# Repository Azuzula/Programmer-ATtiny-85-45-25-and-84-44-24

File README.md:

# Programmer ATtiny 85/45/25 and 84/44/24
Scheme and PCB made in the Eagle 8.7.1
Added Gerber files.

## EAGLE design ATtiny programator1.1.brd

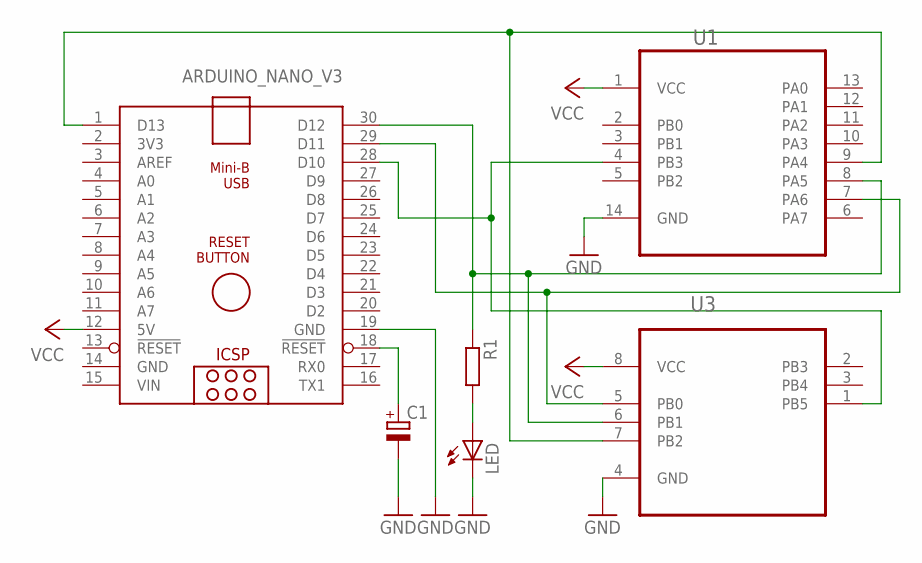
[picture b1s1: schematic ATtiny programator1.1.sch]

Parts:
ARDUINO_NANO_V3: ARDUINO_NANO
C1: CPOL-EUTT2D4; TT2D4
LED: LED3MM
R1: R0204/7; 0204/7
U1: ATTINY84-20PU; DIP254P762X533-14
U3: ATTINY45-20PU; DIP254P762X533-8

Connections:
GND: ARDUINO_NANO_V3.14 (GND), ARDUINO_NANO_V3.19 (GND), C1.-, LED.K (C), U1.14 (GND), U3.4 (GND)
MISO: ARDUINO_NANO_V3.30 (D12), R1.1, U1.8 (PA5), U3.6 (PB1)
MOSI: ARDUINO_NANO_V3.29 (D11), U1.7 (PA6), U3.5 (PB0)
unnamed: LED.A, R1.2
unnamed: ARDUINO_NANO_V3.18 (!RESET), C1.+
SCK: ARDUINO_NANO_V3.1 (D13), U1.9 (PA4), U3.7 (PB2)
SS: ARDUINO_NANO_V3.28 (D10), U1.4 (PB3), U3.1 (PB5)
VCC: ARDUINO_NANO_V3.12 (5V), U1.1 (VCC), U3.8 (VCC)
VIN: ARDUINO_NANO_V3.15 (VIN)

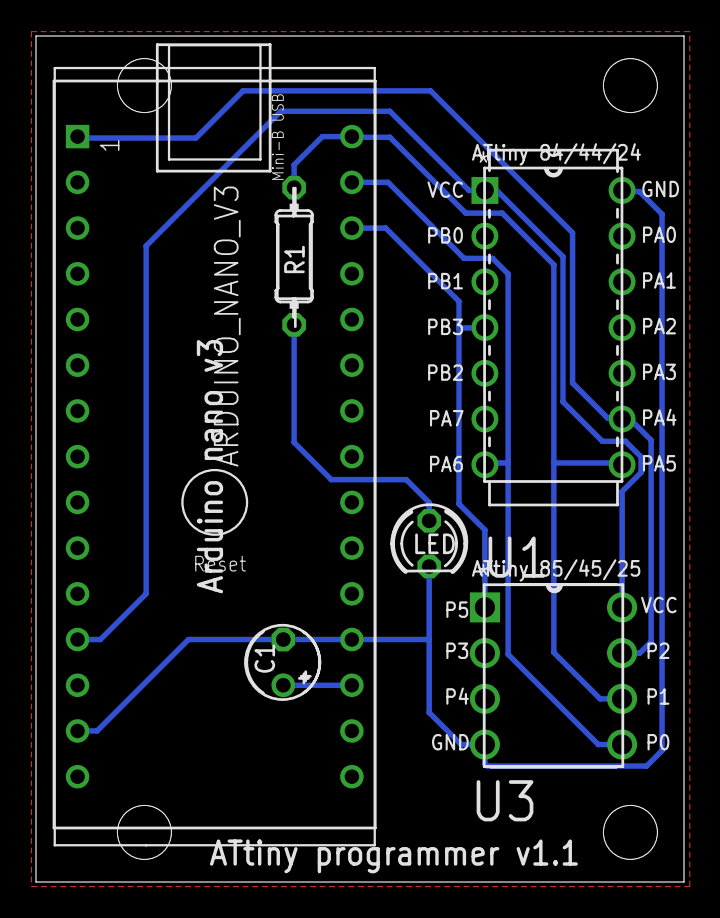
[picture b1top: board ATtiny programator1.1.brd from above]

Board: 2 copper layers, 36.0 x 47.0 mm, 6 parts (0 on the bottom side), 8 nets.

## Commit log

2019-04-02 Add files via upload
    Scheme and PCB in Eagle 8.7.1 + gerber files.
